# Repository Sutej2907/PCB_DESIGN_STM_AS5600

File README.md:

# PCB_DESIGN_STM_AS5600
STM32 BLUE PILL F103C8 AND MAGNETIC ENCODER AS5600 CHIPS INTEGRATED PCB

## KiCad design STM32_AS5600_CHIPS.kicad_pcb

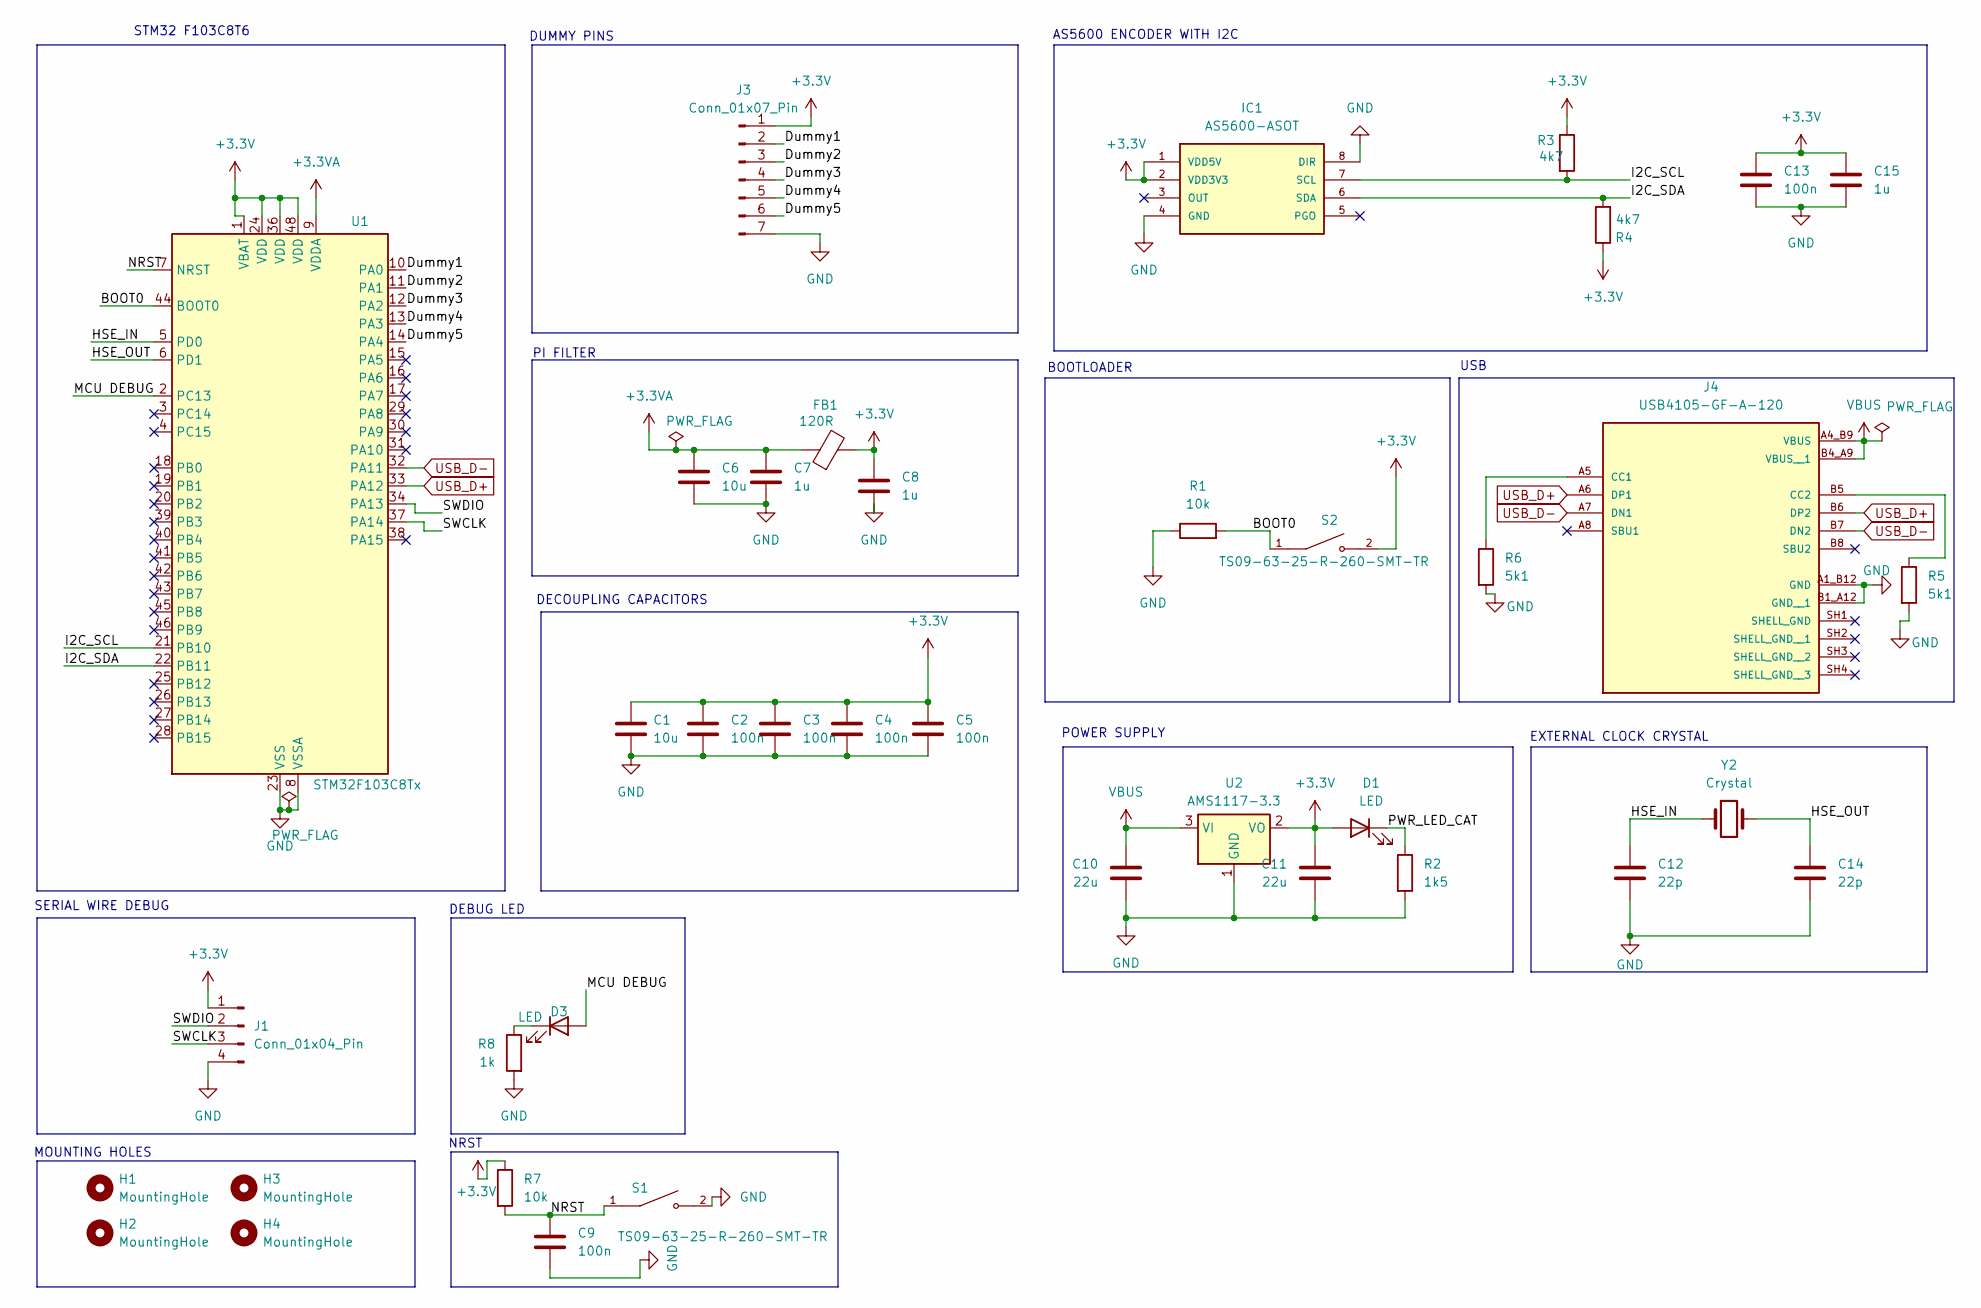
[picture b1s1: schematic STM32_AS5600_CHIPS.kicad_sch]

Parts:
C1, C6: 10u; C_0603_1608Metric
C2, C3, C4, C5, C9, C13: 100n; C_0603_1608Metric
C7, C8, C15: 1u; C_0603_1608Metric
C10, C11: 22u; C_0603_1608Metric
C12, C14: 22p; C_0603_1608Metric
D1, D3: LED; LED_0603_1608Metric
FB1: 120R; FB_LI0603G121R-10
H1, H2, H3, H4: MountingHole; MountingHole_2.2mm_M2
IC1: AS5600-ASOT; SOIC127P600X175-8N; MOUSER_PART_NUMBER 985-AS5600-ASOT
J1: Conn_01x04_Pin; PinHeader_1x04_P2.54mm_Vertical
J3: Conn_01x07_Pin; PinHeader_1x07_P2.54mm_Vertical
J4: USB4105-GF-A-120; GCT_USB4105-GF-A-120; PARTREV B3
R1, R7: 10k; R_0603_1608Metric
R2: 1k5; R_0603_1608Metric
R3, R4: 4k7; R_0603_1608Metric
R5, R6: 5k1; R_0603_1608Metric
R8: 1k; R_0603_1608Metric
S1, S2: TS09-63-25-R-260-SMT-TR; SW_TS09-63-25-R-260-SMT-TR; PARTREV 1.0
U1: STM32F103C8Tx; LQFP-48_7x7mm_P0.5mm
U2: AMS1117-3.3; SOT-223-3_TabPin2
Y2: Crystal; Crystal_SMD_0603-2Pin_6.0x3.5mm_HandSoldering

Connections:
+3.3V: C1.1, C2.1, C3.1, C4.1, C5.1, C8.1, C11.1, C13.1, C15.1, D1.2 (A), FB1.2, IC1.1 (VDD5V), IC1.2 (VDD3V3), J1.1, J3.1, R3.1, R4.1, R7.1, S2.2, U1.1 (VBAT), U1.24 (VDD), U1.36 (VDD), U1.48 (VDD), U2.2 (VO)
+3.3VA: C6.1, C7.1, FB1.1, U1.9 (VDDA)
/BOOT0: R1.2, S2.1, U1.44 (BOOT0)
/Dummy1: J3.2, U1.10 (PA0)
/Dummy2: J3.3, U1.11 (PA1)
/Dummy3: J3.4, U1.12 (PA2)
/Dummy4: J3.5, U1.13 (PA3)
/Dummy5: J3.6, U1.14 (PA4)
/HSE_IN: C12.1, U1.5 (PD0), Y2.1
/HSE_OUT: C14.1, U1.6 (PD1), Y2.2
/I2C_SCL: IC1.7 (SCL), R3.2, U1.21 (PB10)
/I2C_SDA: IC1.6 (SDA), R4.2, U1.22 (PB11)
/MCU DEBUG: D3.2 (A), U1.2 (PC13)
/NRST: C9.1, R7.2, S1.1, U1.7 (NRST)
/PWR_LED_CAT: D1.1 (K), R2.1
/SWCLK: J1.3, U1.37 (PA14)
/SWDIO: J1.2, U1.34 (PA13)
GND: C1.2, C2.2, C3.2, C4.2, C5.2, C6.2, C7.2, C8.2, C9.2, C10.2, C11.2, C12.2, C13.2, C14.2, C15.2, IC1.4 (GND), IC1.8 (DIR), J1.4, J3.7, J4.A1_B12 (GND), J4.B1_A12 (GND__1), R1.1, R2.2, R5.2, R6.2, R8.2, S1.2, U1.8 (VSSA), U1.23 (VSS), U1.35 (VSS), U1.47 (VSS), U2.1 (GND)
unnamed: D3.1 (K), R8.1
unnamed: J4.A5 (CC1), R6.1
unnamed: J4.B5 (CC2), R5.1
USB_D+: J4.A6 (DP1), J4.B6 (DP2), U1.33 (PA12)
USB_D-: J4.A7 (DN1), J4.B7 (DN2), U1.32 (PA11)
VBUS: C10.1, J4.A4_B9 (VBUS), J4.B4_A9 (VBUS__1), U2.3 (VI)

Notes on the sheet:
DECOUPLING CAPACITORS
MOUNTING HOLES
BOOTLOADER
EXTERNAL CLOCK CRYSTAL
USB
STM32 F103C8T6
NRST
DEBUG LED
AS5600 ENCODER WITH I2C
POWER SUPPLY
PI FILTER
DUMMY PINS
SERIAL WIRE DEBUG

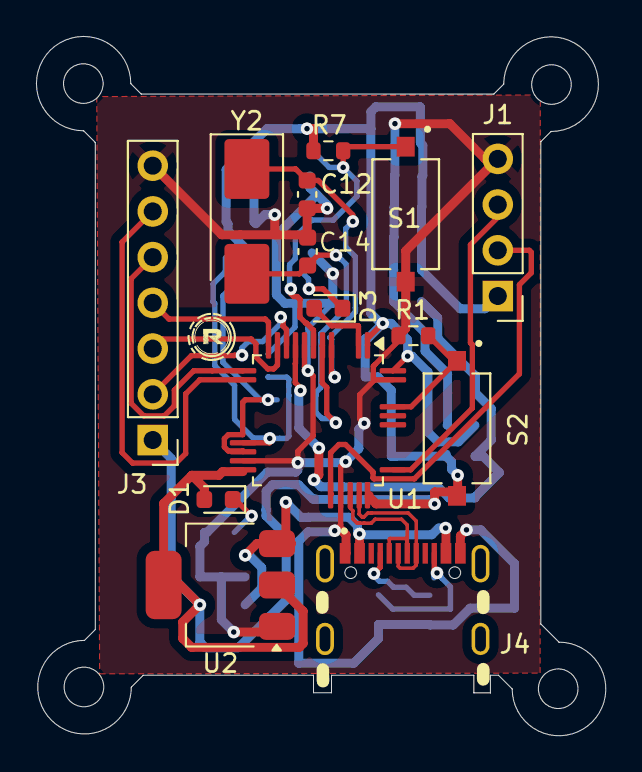
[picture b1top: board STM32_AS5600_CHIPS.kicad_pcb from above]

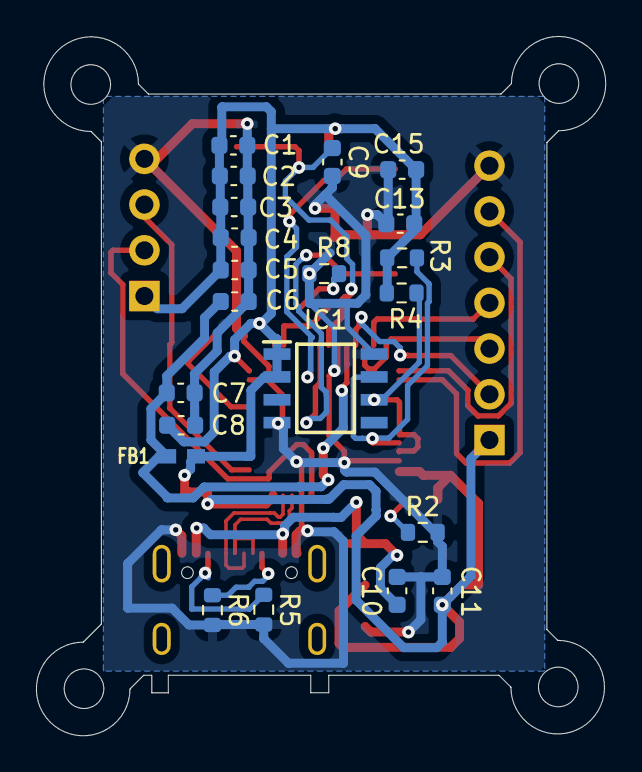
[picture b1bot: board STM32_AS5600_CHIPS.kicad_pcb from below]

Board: 2 copper layers, 31.6 x 38.8 mm, 39 parts (21 on the bottom side), 24 nets.

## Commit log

2026-02-18 Add files via upload
    1st Commit
2026-02-19 Add files via upload
    2nd Commit
2026-02-20 Add files via upload
    dfm check done commit, but usb lot idth issue
2026-02-20 MOUNTING HOLES UPDATED
